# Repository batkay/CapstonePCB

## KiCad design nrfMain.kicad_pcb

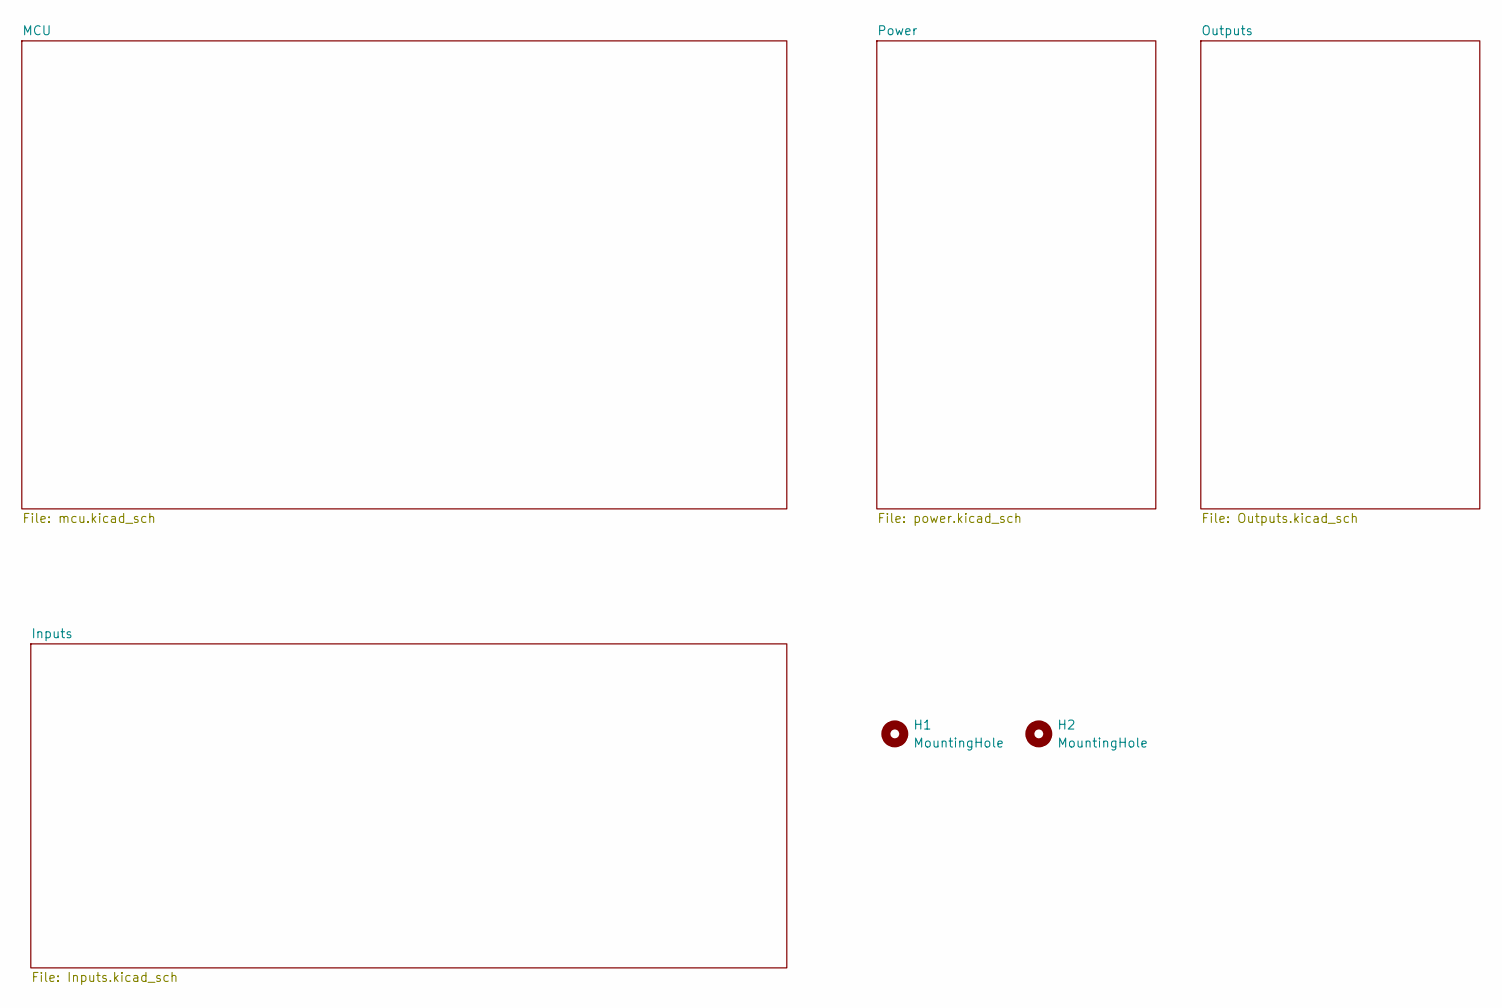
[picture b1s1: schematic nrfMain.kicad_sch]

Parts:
H1, H2: MountingHole; MountingHole_2.5mm

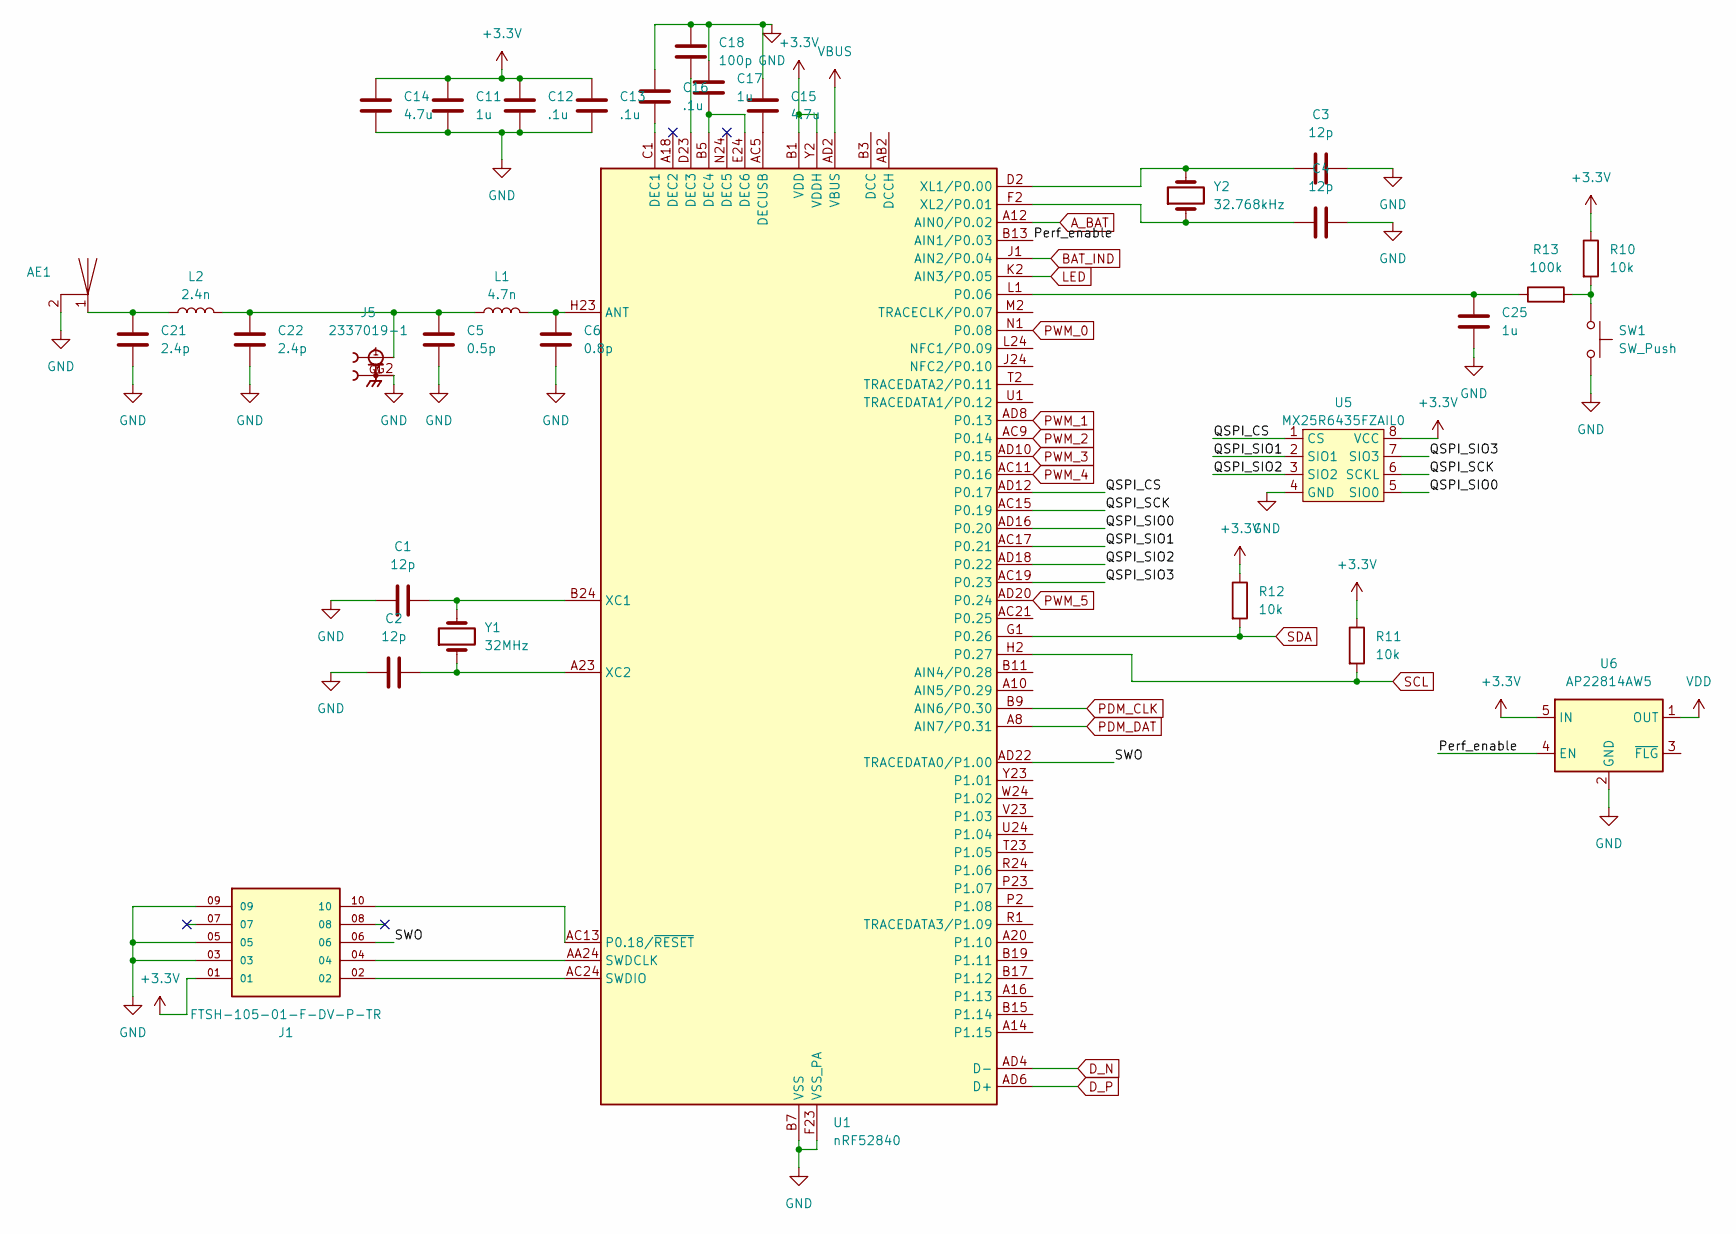
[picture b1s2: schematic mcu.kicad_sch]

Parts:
AE1: Trace Antenna
C1, C2, C3, C4: 12p; C_0603_1608Metric; MPN C107034; LCSC PN C107034
C5: 0.5p; C_0603_1608Metric; MPN C162254; LCSC PN C162254
C6: 0.8p; C_0603_1608Metric; MPN C907996; LCSC PN C907996
C11, C17, C25: 1u; C_0603_1608Metric; MPN C15849; LCSC PN C15849
C12, C13, C16: .1u; C_0603_1608Metric; MPN C14663; LCSC PN C14663
C14, C15: 4.7u; C_0603_1608Metric; MPN C19666; LCSC PN C19666
C18: 100p; C_0603_1608Metric; MPN C14665; LCSC PN C14665
C21, C22: 2.4p; C_0603_1608Metric; MPN C710896; LCSC PN C710896
J1: FTSH-105-01-F-DV-P-TR; SAMTEC_FTSH-105-01-F-DV-P-TR; PARTREV R; LCSC PN C5136979
J5: 2337019-1; TE_2337019-1; PARTREV A4
L1: 4.7n; L_0603_1608Metric; MPN C98078; LCSC PN C98078
L2: 2.4n; L_0603_1608Metric; MPN C2042508; LCSC PN C2042508
R10, R11, R12: 10k; R_0603_1608Metric; MPN C98220; LCSC PN C98220
R13: 100k; R_0603_1608Metric; MPN C14675; LCSC PN C14675
SW1: SW_Push; SW_PUSH_6mm; LCSC PN C393938
U1: nRF52840; Nordic_AQFN-73-1EP_7x7mm_P0.5mm; Part Number NRF52840-QIAA-R; LCSC PN C190794
U5: MX25R6435FZAIL0; WSON-8-1EP_4x4mm_P0.8mm_EP1.98x3mm; Part Number MX25R6435FZAIL0; LCSC PN C2802847
U6: AP22814AW5; SOT-23-5; MPN C2680321; LCSC PN C2680321
Y1: 32MHz; Crystal_SMD_HC49-SD; Part Number HY32M49SSMDOB2R20; LCSC PN C5265796
Y2: 32.768kHz; Crystal_SMD_3215-2Pin_3.2x1.5mm; Part Number Q13FC13500004; LCSC PN C32346

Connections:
+3.3V: C11.1, C12.1, C13.1, C14.1, J1.01, R10.1, R11.1, R12.1, U1.A22 (VDD), U1.AD14 (VDD), U1.AD23 (VDD), U1.B1 (VDD), U1.W1 (VDD), U1.Y2 (VDDH), U5.8 (VCC), U6.5 (IN); also elsewhere on the board
/MCU/Perf_enable: U1.B13 (AIN1/P0.03), U6.4 (EN)
/MCU/QSPI_CS: U1.AD12 (P0.17), U5.1 (CS)
/MCU/QSPI_SCK: U1.AC15 (P0.19), U5.6 (SCKL)
/MCU/QSPI_SIO0: U1.AD16 (P0.20), U5.5 (SIO0)
/MCU/QSPI_SIO1: U1.AC17 (P0.21), U5.2 (SIO1)
/MCU/QSPI_SIO2: U1.AD18 (P0.22), U5.3 (SIO2)
/MCU/QSPI_SIO3: U1.AC19 (P0.23), U5.7 (SIO3)
/MCU/SWO: J1.06, U1.AD22 (TRACEDATA0/P1.00)
A_BAT: U1.A12 (AIN0/P0.02); also elsewhere on the board
BAT_IND: U1.J1 (AIN2/P0.04); also elsewhere on the board
D_N: U1.AD4 (D-); also elsewhere on the board
D_P: U1.AD6 (D+); also elsewhere on the board
GND: AE1.2, C1.1, C2.1, C3.2, C4.2, C5.2, C6.2, C11.2, C12.2, C13.2, C14.2, C15.2, C16.1, C17.1, C18.1, C21.2, C22.2, C25.2, J1.03, J1.05, J1.09, J5.G1, J5.G2, SW1.2, U1.B7 (VSS), U1.EP (VSS), U1.F23 (VSS_PA), U5.4 (GND), U6.2 (GND); also elsewhere on the board
LED: U1.K2 (AIN3/P0.05); also elsewhere on the board
unnamed: AE1.1, C21.1, L2.1
unnamed: C5.1, C22.1, J5.1, L1.1, L2.2
unnamed: R10.2, R13.2, SW1.1
unnamed: C6.1, L1.2, U1.H23 (ANT)
unnamed: C16.2, U1.C1 (DEC1)
unnamed: C18.2, U1.D23 (DEC3)
unnamed: C17.2, U1.B5 (DEC4), U1.E24 (DEC6)
unnamed: C15.1, U1.AC5 (DECUSB)
unnamed: C25.1, R13.1, U1.L1 (P0.06)
unnamed: J1.10, U1.AC13 (P0.18/~RESET)
unnamed: J1.04, U1.AA24 (SWDCLK)
unnamed: J1.02, U1.AC24 (SWDIO)
unnamed: C1.2, U1.B24 (XC1), Y1.2
unnamed: C2.2, U1.A23 (XC2), Y1.1
unnamed: C3.1, U1.D2 (XL1/P0.00), Y2.2
unnamed: C4.1, U1.F2 (XL2/P0.01), Y2.1
PDM_CLK: U1.B9 (AIN6/P0.30); also elsewhere on the board
PDM_DAT: U1.A8 (AIN7/P0.31); also elsewhere on the board
PWM_0: U1.N1 (P0.08); also elsewhere on the board
PWM_1: U1.AD8 (P0.13); also elsewhere on the board
PWM_2: U1.AC9 (P0.14); also elsewhere on the board
PWM_3: U1.AD10 (P0.15); also elsewhere on the board
PWM_4: U1.AC11 (P0.16); also elsewhere on the board
PWM_5: U1.AD20 (P0.24); also elsewhere on the board
SCL: R11.2, U1.H2 (P0.27); also elsewhere on the board
SDA: R12.2, U1.G1 (P0.26); also elsewhere on the board
VBUS: U1.AD2 (VBUS); also elsewhere on the board
VDD: U6.1 (OUT); also elsewhere on the board

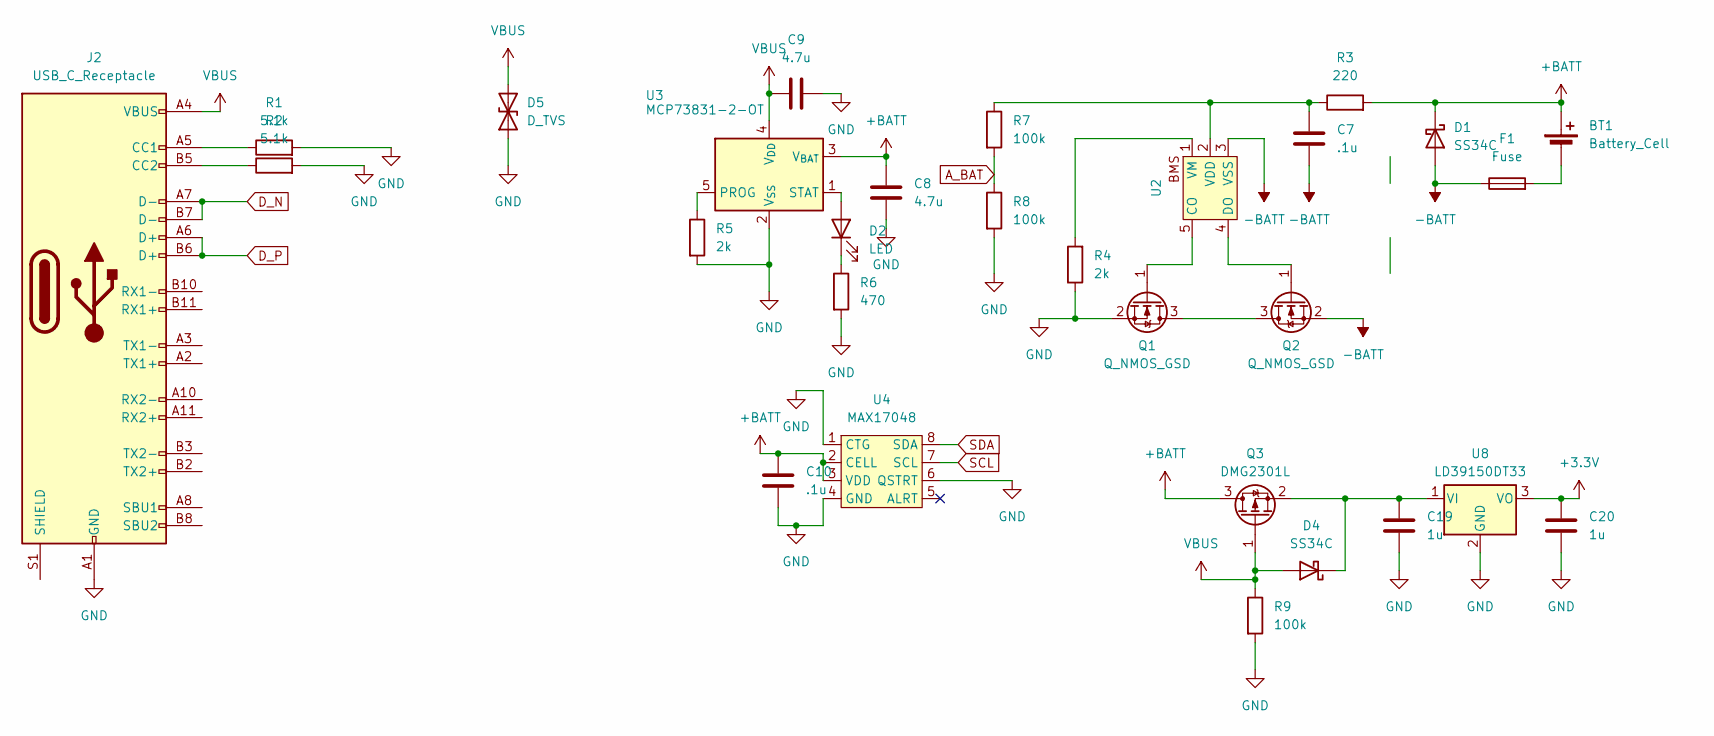
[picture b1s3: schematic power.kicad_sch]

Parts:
BT1: Battery_Cell; JST_PH_S2B-PH-K_1x02_P2.00mm_Horizontal; Part Number S2B-PH-K-S-GW; LCSC PN C157932
C7, C10: .1u; C_0603_1608Metric; MPN C14663; LCSC PN C14663
C8, C9: 4.7u; C_0603_1608Metric; MPN C19666; LCSC PN C19666
C19, C20: 1u; C_0603_1608Metric; MPN C15849; LCSC PN C15849
D1, D4: SS34C; D_SMC; MPN C13763; LCSC PN C13763
D2: LED; LED_0805_2012Metric; MPN C965817; LCSC PN C965817
D5: D_TVS; D_0402_1005Metric; Part Number TPD1E10B06DPYR; LCSC PN C48260
F1: Fuse; Fuse_1210_3225Metric; Part Number Shenzhen JDT Fuse ASMD1210-075; LCSC PN C135349
J2: USB_C_Receptacle; USB_C_Receptacle_GCT_USB4105-xx-A_16P_TopMnt_Horizontal; Part Number MC-107D; LCSC PN C2874568
Q1, Q2: Q_NMOS_GSD; TSOT-23; Part Number DMG3414U-7; LCSC PN C260927
Q3: DMG2301L; SOT-23; MPN C102619; LCSC PN C102619
R1, R2: 5.1k; R_0603_1608Metric; MPN C122969; LCSC PN C122969
R3: 220; R_0603_1608Metric; MPN C107696; LCSC PN C107696
R4, R5: 2k; R_0603_1608Metric; MPN C105576; LCSC PN C105576
R6: 470; R_0603_1608Metric; MPN C114669; LCSC PN C114669
R7, R8: 100k; R_0603_1608Metric; MPN C19666; LCSC PN C14675
R9: 100k; R_0603_1608Metric; MPN C14675; LCSC PN C14675
U2: SOT-23-5; Part Number S-8211CAZ-M5T1G; LCSC PN C5881307
U3: MCP73831-2-OT; SOT-23-5; Part Number MCP73831T-2ACI/OT; LCSC PN C424093
U4: MAX17048; TDFN-8-1EP_2x2mm_P0.5mm_EP0.8x1.2mm; MPN C2682616; LCSC PN C2682616
U8: LD39150DT33; TO-252-3_TabPin2; MPN C155559; LCSC PN C155559

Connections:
+3.3V: C20.1, U8.3 (VO); also elsewhere on the board
+BATT: BT1.1 (+), C8.1, C10.1, D1.1 (K), Q3.3 (D), R3.2, U3.3 (V_{BAT}), U4.2 (CELL), U4.3 (VDD)
-BATT: C7.2, D1.2 (A), F1.1, Q2.2 (S), U2.3 (VSS)
A_BAT: R7.2, R8.1; also elsewhere on the board
D_N: J2.A7 (D-), J2.B7 (D-); also elsewhere on the board
D_P: J2.A6 (D+), J2.B6 (D+); also elsewhere on the board
GND: C8.2, C9.2, C10.2, C19.2, C20.2, D5.1 (A1), J2.A1 (GND), J2.A12 (GND), J2.B1 (GND), J2.B12 (GND), Q1.2 (S), R1.2, R2.2, R4.1, R5.2, R6.2, R8.2, R9.2, U3.2 (V_{SS}), U4.1 (CTG), U4.4 (GND), U4.6 (QSTRT), U8.2 (GND); also elsewhere on the board
unnamed: BT1.2 (-), F1.2
unnamed: D2.2 (A), U3.1 (STAT)
unnamed: D2.1 (K), R6.1
unnamed: C19.1, D4.1 (K), Q3.2 (S), U8.1 (VI)
unnamed: J2.A5 (CC1), R1.1
unnamed: J2.B5 (CC2), R2.1
unnamed: Q1.3 (D), Q2.3 (D)
unnamed: Q1.1 (G), U2.5 (CO)
unnamed: Q2.1 (G), U2.4 (DO)
unnamed: C7.1, R3.1, R7.1, U2.2 (VDD)
unnamed: R4.2, U2.1 (VM)
unnamed: R5.1, U3.5 (PROG)
SCL: U4.7 (SCL); also elsewhere on the board
SDA: U4.8 (SDA); also elsewhere on the board
VBUS: C9.1, D4.2 (A), D5.2 (A2), J2.A4 (VBUS), J2.A9 (VBUS), J2.B4 (VBUS), J2.B9 (VBUS), Q3.1 (G), R9.1, U3.4 (V_{DD}); also elsewhere on the board

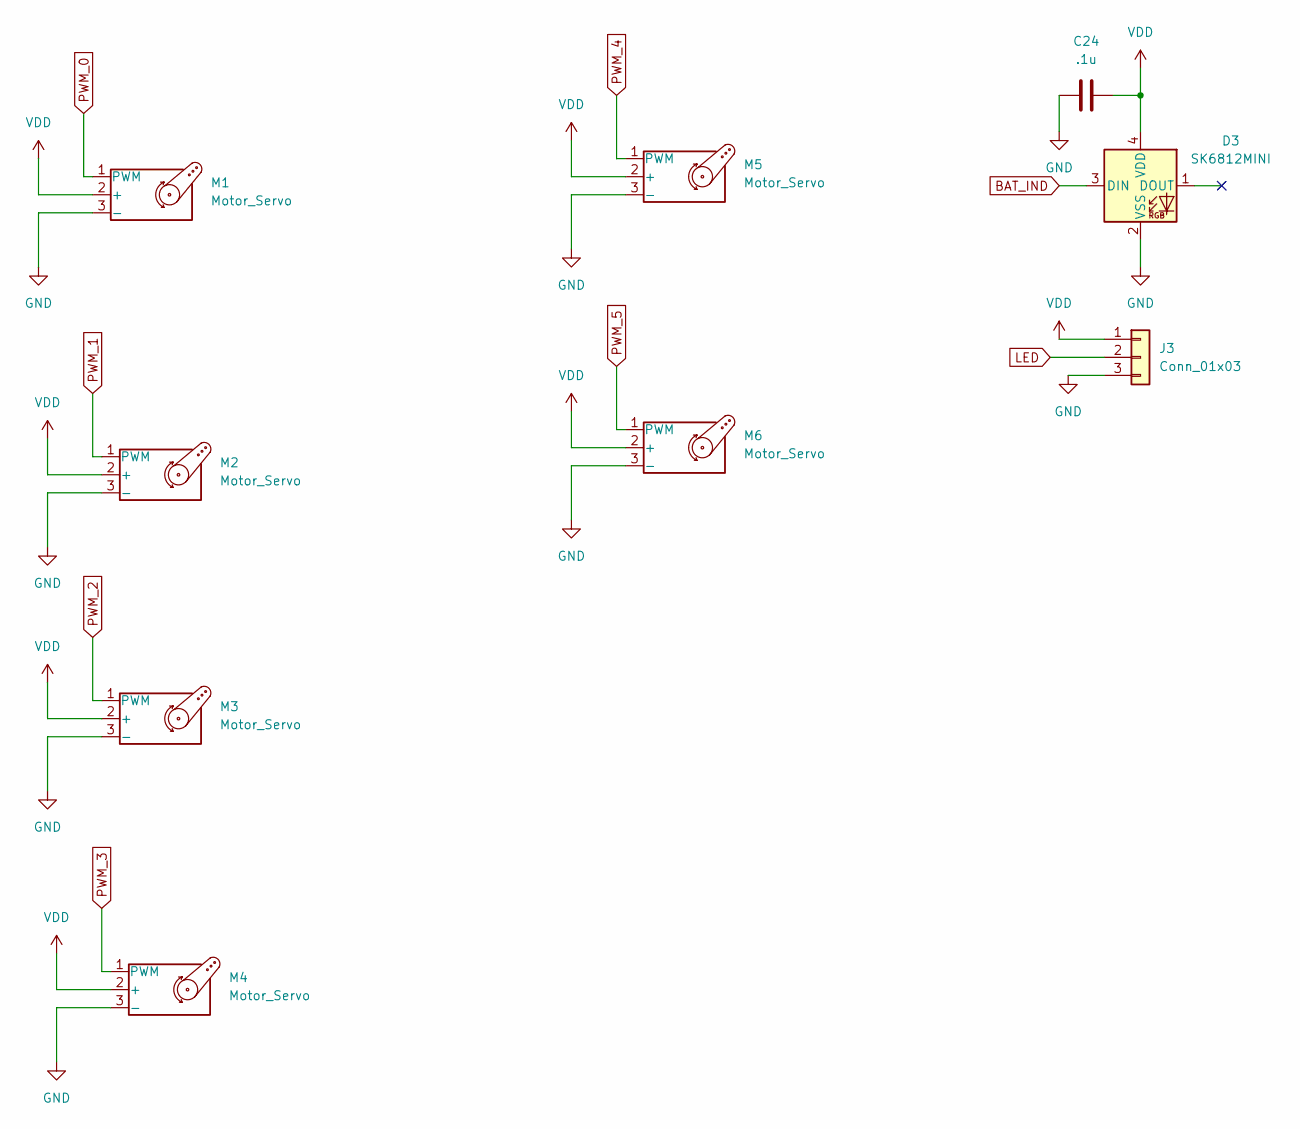
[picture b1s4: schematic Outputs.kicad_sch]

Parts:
C24: .1u; C_0603_1608Metric; MPN C14663; LCSC PN C14663
D3: SK6812MINI; LED_SK6812MINI_PLCC4_3.5x3.5mm_P1.75mm; MPN C2922787; LCSC PN C2922787
J3: Conn_01x03; PinHeader_1x03_P2.54mm_Horizontal
M1, M2, M3, M4, M5, M6: Motor_Servo; PinHeader_1x03_P2.54mm_Vertical

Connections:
BAT_IND: D3.3 (DIN); also elsewhere on the board
GND: C24.1, D3.2 (VSS), J3.3, M1.3 (-), M2.3 (-), M3.3 (-), M4.3 (-), M5.3 (-), M6.3 (-); also elsewhere on the board
LED: J3.2; also elsewhere on the board
PWM_0: M1.1 (PWM); also elsewhere on the board
PWM_1: M2.1 (PWM); also elsewhere on the board
PWM_2: M3.1 (PWM); also elsewhere on the board
PWM_3: M4.1 (PWM); also elsewhere on the board
PWM_4: M5.1 (PWM); also elsewhere on the board
PWM_5: M6.1 (PWM); also elsewhere on the board
VDD: C24.2, D3.4 (VDD), J3.1, M1.2 (+), M2.2 (+), M3.2 (+), M4.2 (+), M5.2 (+), M6.2 (+); also elsewhere on the board

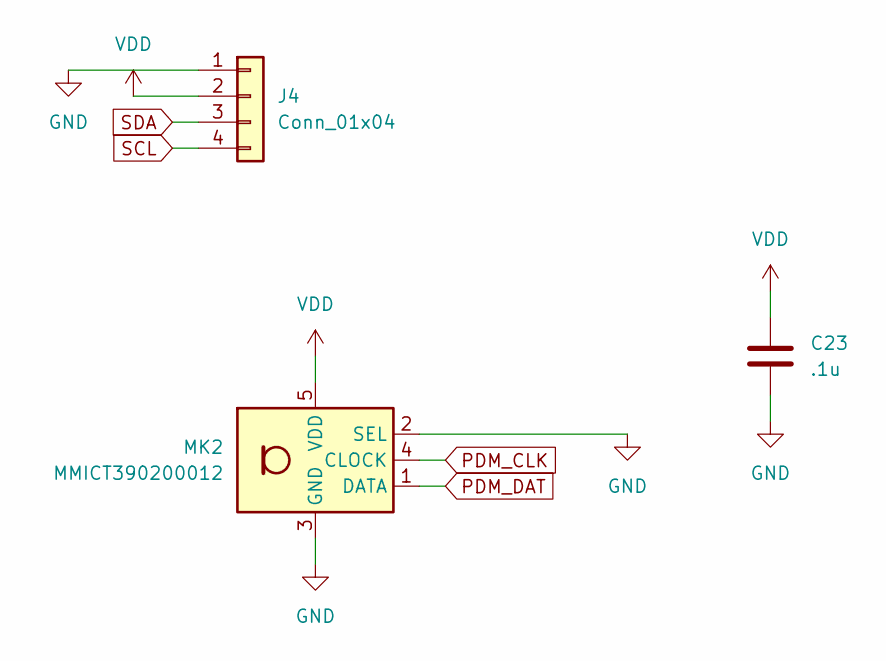
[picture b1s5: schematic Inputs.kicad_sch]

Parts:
C23: .1u; C_0603_1608Metric; MPN C14663; LCSC PN C14663
J4: Conn_01x04; JST_SH_BM04B-SRSS-TB_1x04-1MP_P1.00mm_Vertical; Part Number JST BM04B-SRSS-TB(LF)(SN); LCSC PN C160390
MK2: MMICT390200012; Knowles_LGA-5_3.5x2.65mm; Part Number MMICT390200012; LCSC PN C3171752

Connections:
GND: C23.2, J4.1, MK2.2 (SEL), MK2.3 (GND); also elsewhere on the board
PDM_CLK: MK2.4 (CLOCK); also elsewhere on the board
PDM_DAT: MK2.1 (DATA); also elsewhere on the board
SCL: J4.4; also elsewhere on the board
SDA: J4.3; also elsewhere on the board
VDD: C23.1, J4.2, MK2.5 (VDD); also elsewhere on the board

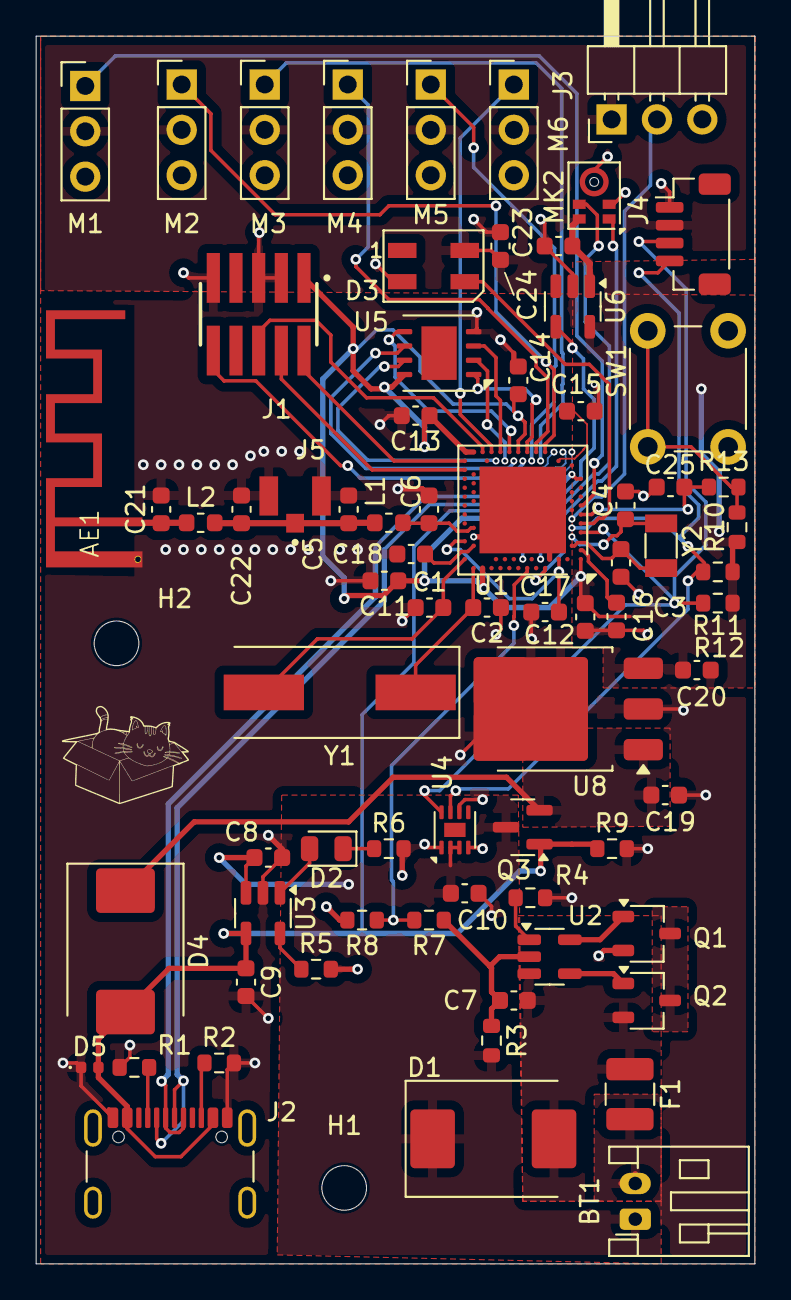
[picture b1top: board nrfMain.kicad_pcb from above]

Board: 4 copper layers, 40.2 x 68.8 mm, 75 parts (0 on the bottom side), 57 nets.

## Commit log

2025-02-04 initial
2025-02-05 Added antenna
2025-02-05 Setup charging
2025-02-16 Added outputs page
2025-02-27 Added output headers
2025-02-27 Added pmos and regulator
2025-02-27 Switch regulator to 1.5A
2025-03-01 Added impedance match, gitignore
2025-03-01 Added TVS diode
2025-03-03 Added microphone, fuse
2025-03-06 finished schematic
2025-03-06 PCB layout
2025-03-07 Added USB routing
2025-03-07 Added LCSC PN for bms
2025-03-09 Added mounting holes and other final touches
2025-03-10 step file
2025-03-14 Made modifications from fabrication
